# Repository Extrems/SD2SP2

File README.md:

# SD2SP2

This PCB allows a microSD card to be adapted into the Serial Port 2 of the GameCube.

The PCB must be ordered in 1.2mm thickness. Surface finish must be ENIG at minimum. I recommend https://jlcpcb.com for PCB production.

BOM:

C1: 0805 22u Capactior (10V Min) - DigiKey Part# 1276-6780-1-ND

J1: MicroSD Slot - DigiKey Part# WM14405CT-ND

U1: OR Gate IC - DigiKey Part# 296-1093-1-ND

Special thanks to:  
 * MockyLock for the idea  
 * Extrems & emu_kidid for doing the real work needed to make this possible

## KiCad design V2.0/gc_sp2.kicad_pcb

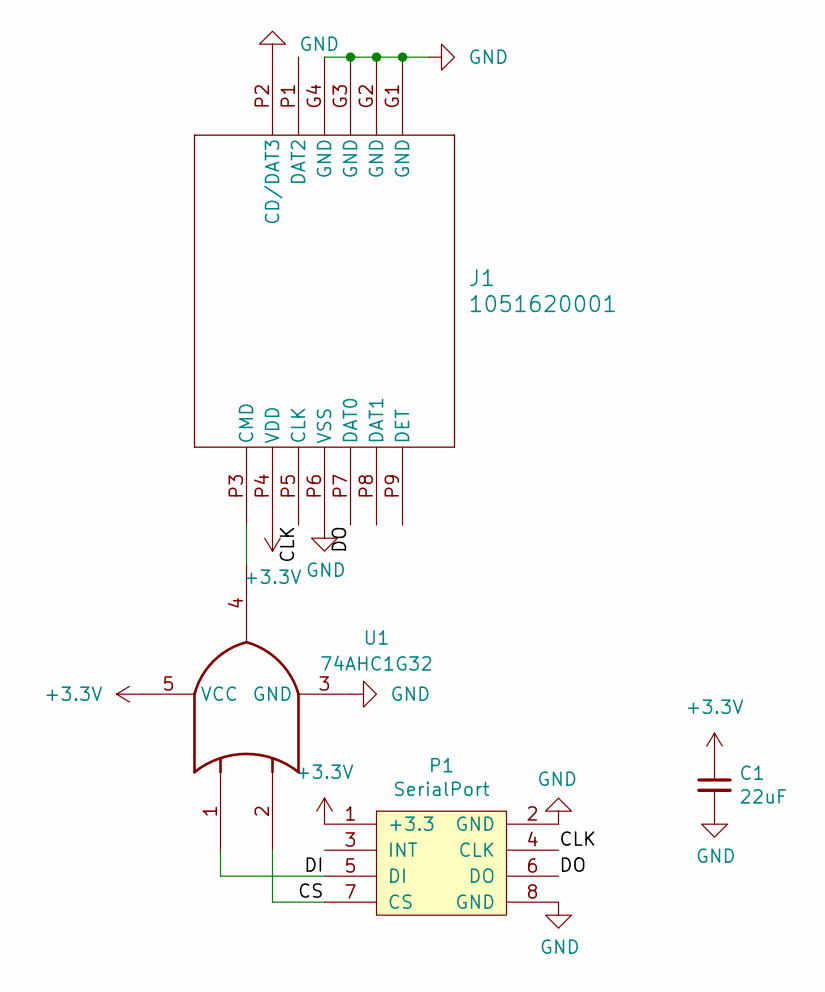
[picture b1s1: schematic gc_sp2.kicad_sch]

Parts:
C1: 22uF; C_0805_HandSoldering
J1: 1051620001; 105162-0001_MOL
P1: SerialPort; SP2_FootPrint
U1: 74AHC1G32; SC-74A-5_1.55x2.9mm_P0.95mm

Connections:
+3.3V: C1.1, J1.P4 (VDD), P1.1 (+3.3), U1.5 (VCC)
/CLK: J1.P5 (CLK), P1.4 (CLK)
/CS: P1.7 (CS), U1.2
/DI: P1.5 (DI), U1.1
/DO: J1.P7 (DAT0), P1.6 (DO)
GND: C1.2, J1.G1 (GND), J1.G2 (GND), J1.G3 (GND), J1.G4 (GND), J1.P2 (CD/DAT3), J1.P6 (VSS), P1.2 (GND), P1.8 (GND), U1.3 (GND)
unnamed: J1.P3 (CMD), U1.4

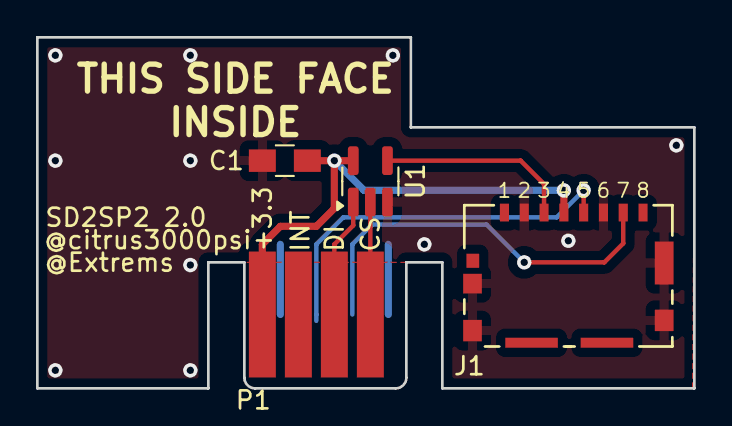
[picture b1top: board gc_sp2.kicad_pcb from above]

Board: 2 copper layers, 36.5 x 19.5 mm, 4 parts (0 on the bottom side), 7 nets.
